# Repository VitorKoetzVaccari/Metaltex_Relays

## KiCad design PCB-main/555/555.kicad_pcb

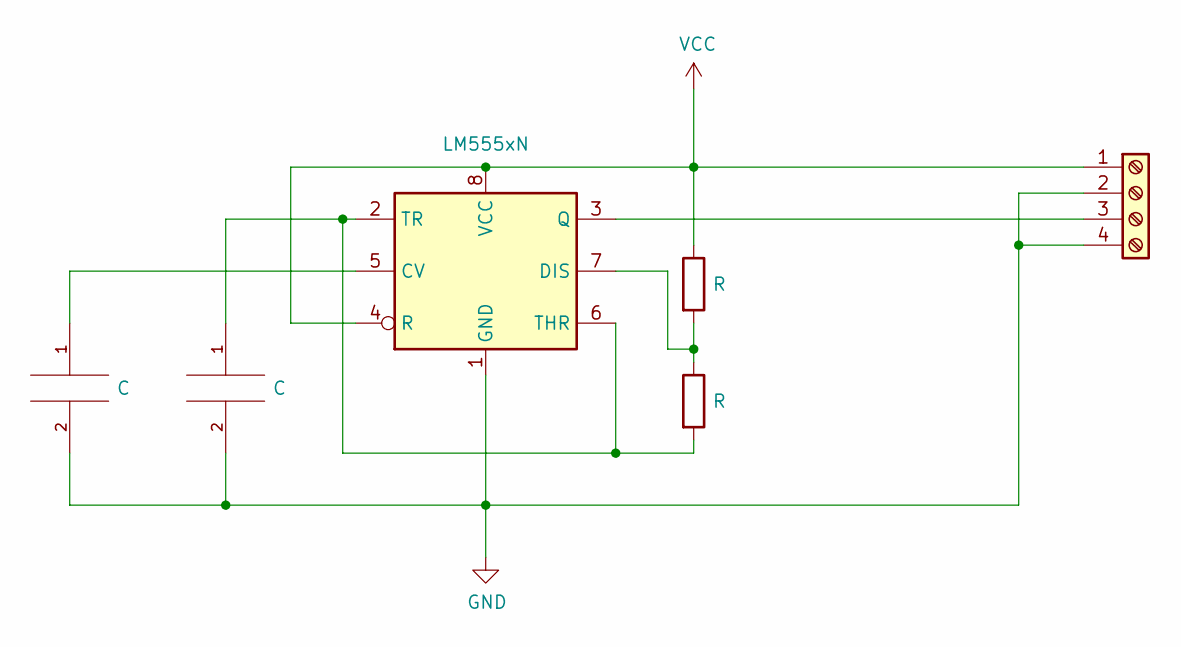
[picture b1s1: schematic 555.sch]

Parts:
C1: C; CP_Radial_D12.5mm_P5.00mm
C2: C; C_Disc_D5.0mm_W2.5mm_P2.50mm
R1, R2: R; R_Axial_DIN0207_L6.3mm_D2.5mm_P10.16mm_Horizontal
U1: LM555xN; DIP-8_W7.62mm

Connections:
GND: C1.2, C2.2, U1.1 (GND)
unnamed: C1.1, R2.2, U1.2 (TR), U1.6 (THR)
unnamed: C2.1, U1.5 (CV)
unnamed: R1.2, R2.1, U1.7 (DIS)
VCC: R1.1, U1.4 (R), U1.8 (VCC)

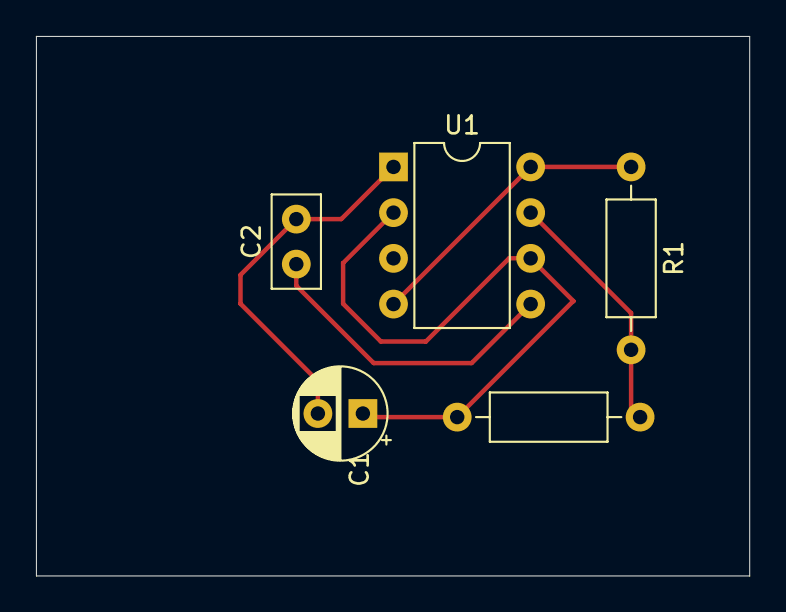
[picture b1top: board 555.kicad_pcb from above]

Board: 2 copper layers, 39.6 x 30.0 mm, 5 parts (0 on the bottom side), 5 nets.
